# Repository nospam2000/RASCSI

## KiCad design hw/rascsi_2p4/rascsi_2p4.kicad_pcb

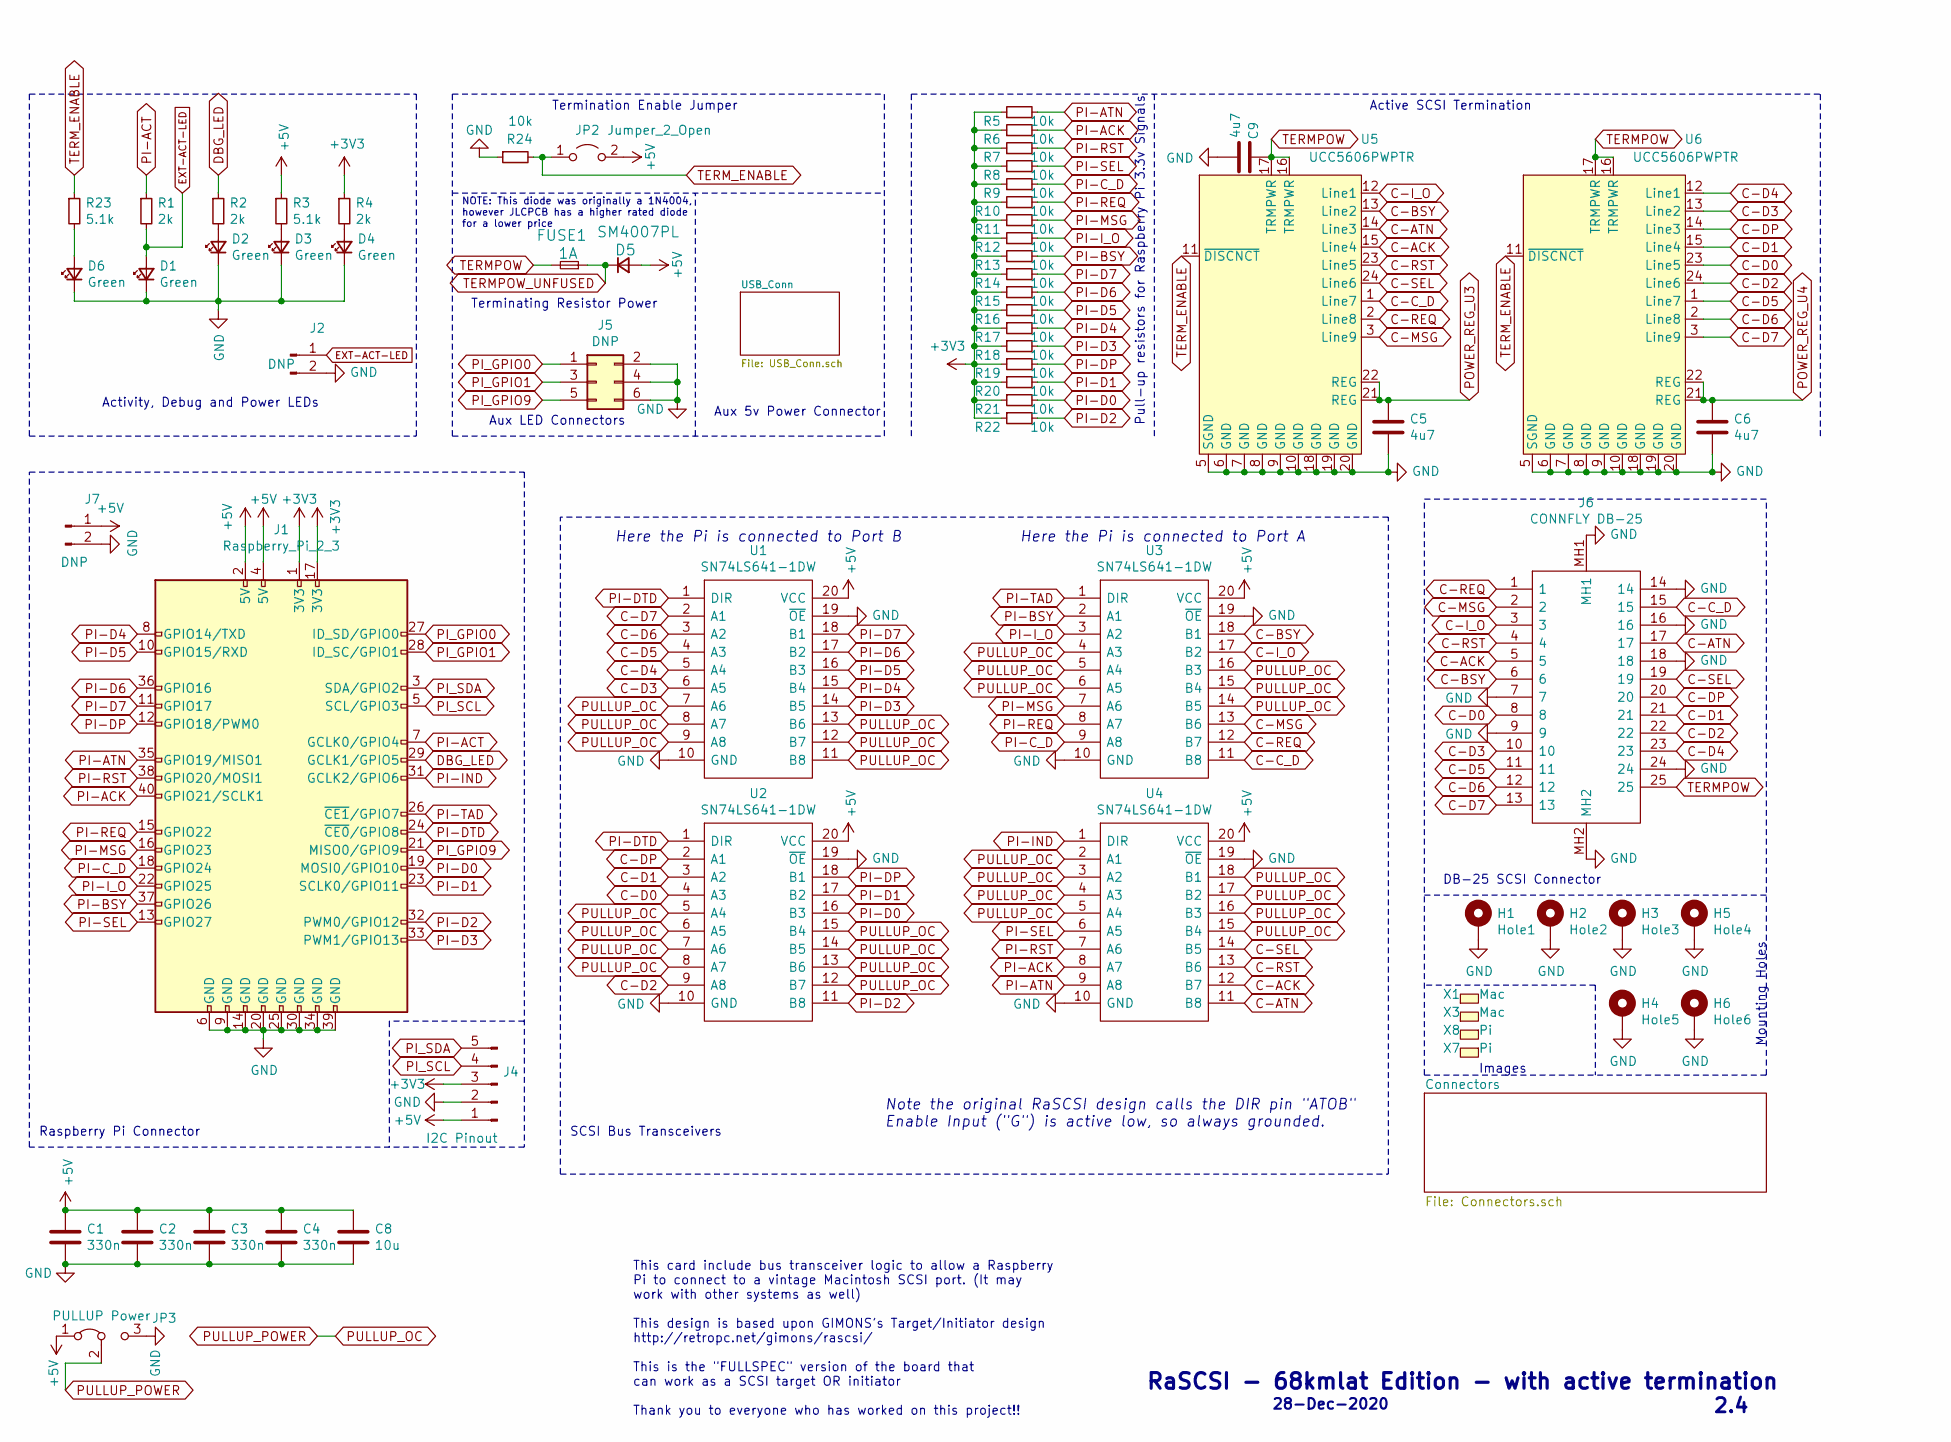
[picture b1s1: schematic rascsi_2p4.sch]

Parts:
C1, C2, C3, C4: 330n; C_0805_2012Metric; Manufacturer_Part_Number 0805B334K500NT; LCSC C1740
C5, C6, C9: 4u7; C_0805_2012Metric; Manufacturer_Part_Number CL21A475KAQNNNE; LCSC C1779
C8: 10u; C_0805_2012Metric; Manufacturer_Part_Number CL21A106KAYNNNE; LCSC C15850
D1, D2, D3, D4, D6: Green; LED_0805_2012Metric; Manufacturer_Part_Number C2297; LCSC C2297
D5: SM4007PL; D_SOD-123F; Manufacturer_Part_Number SM4007PL; LCSC C64898
FUSE1: 1A; Fuse_1206_3216Metric; Manufacturer_Part_Number 12B1100B; LCSC C182974
H1: Hole1; MountingHole_2.7mm_M2.5_Pad_Via; Manufacturer_Part_Number DNP; LCSC DNP
H2: Hole2; MountingHole_2.7mm_M2.5_Pad_Via; Manufacturer_Part_Number DNP; LCSC DNP
H3: Hole3; MountingHole_2.7mm_M2.5_Pad_Via; Manufacturer_Part_Number DNP; LCSC DNP
H4: Hole5; MountingHole_2.7mm_M2.5_Pad_Via; Manufacturer_Part_Number DNP; LCSC DNP
H5: Hole4; MountingHole_2.7mm_M2.5_Pad_Via; Manufacturer_Part_Number DNP; LCSC DNP
H6: Hole6; MountingHole_2.7mm_M2.5_Pad_Via; Manufacturer_Part_Number DNP; LCSC DNP
J1: Raspberry_Pi_2_3; PinSocket_2x20_P2.54mm_Vertical; Manufacturer_Part_Number C50982; LCSC C50982
J2: DNP; PinHeader_1x02_P2.54mm_Horizontal; Manufacturer_Part_Number DNP; LCSC DNP
J4: I2C Pinout; PinSocket_1x05_P2.54mm_Vertical; Manufacturer_Part_Number C50950; LCSC C50950
J5: DNP; PinHeader_2x03_P2.54mm_Vertical; Manufacturer_Part_Number DNP; LCSC DNP
J6: CONNFLY DB-25; L717SDB25PA4CH4F_JLCPCB_hand_mount; Manufacturer_Part_Number DS1037-25FNAKT74-0CC; LCSC C77838
J7: DNP; PinHeader_1x02_P2.54mm_Vertical; Manufacturer_Part_Number DNP; LCSC DNP
JP2: Jumper_2_Open; PinHeader_1x02_P2.54mm_Horizontal
JP3: PULLUP Power; SolderJumper-3_P1.3mm_Bridged12_RoundedPad1.0x1.5mm; Manufacturer_Part_Number DNP; LCSC DNP
R1, R2, R4: 2k; R_0402_1005Metric; Manufacturer_Part_Number 0402WGF2001TCE; LCSC C4109
R3, R23: 5.1k; R_0402_1005Metric; Manufacturer_Part_Number 0402WGF5101TCE; LCSC C25905
R5, R6, R7, R8, R9, R10, R11, R12, R13, R14, R15, R16, R17, R18, R19, R20, R21, R22, R24: 10k; R_0402_1005Metric; Manufacturer_Part_Number 0402WGF1002TCE; LCSC C25744
U1, U2, U3, U4: SN74LS641-1DW; SOIC-20W_7.5x12.8mm_P1.27mm; Mouser Part Number 595-SN74LS641-1DW
U5, U6: UCC5606PWPTR; TSSOP-24_6.1x7.8mm_P0.65mm; LCSC C2649373
X1, X3: Mac; mac_happy_small; Manufacturer_Part_Number N/A; LCSC N/A
X7: Pi; pi_logo; Manufacturer_Part_Number N/A; LCSC N/A
X8: Pi; scsi_logo; Manufacturer_Part_Number N/A; LCSC N/A

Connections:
+3V3: J1.1 (3V3), J1.17 (3V3), J4.3, R4.1, R5.1, R6.1, R7.1, R8.1, R9.1, R10.1, R11.1, R12.1, R13.1, R14.1, R15.1, R16.1, R17.1, R18.1, R19.1, R20.1, R21.1, R22.1
+5V: C1.1, C2.1, C3.1, C4.1, C8.1, D5.2 (A), J1.2 (5V), J1.4 (5V), J4.1, J7.1, JP2.2 (B), JP3.1 (A), R3.1, U1.20 (VCC), U2.20 (VCC), U3.20 (VCC), U4.20 (VCC); also elsewhere on the board
C-ACK: J6.5, U4.12 (B7), U5.15 (Line4); also elsewhere on the board
C-ATN: J6.17, U4.11 (B8), U5.14 (Line3); also elsewhere on the board
C-BSY: J6.6, U3.18 (B1), U5.13 (Line2); also elsewhere on the board
C-C_D: J6.15, U3.11 (B8), U5.1 (Line7); also elsewhere on the board
C-D0: J6.8, U2.4 (A3), U6.23 (Line5); also elsewhere on the board
C-D1: J6.21, U2.3 (A2), U6.15 (Line4); also elsewhere on the board
C-D2: J6.22, U2.9 (A8), U6.24 (Line6); also elsewhere on the board
C-D3: J6.10, U1.6 (A5), U6.13 (Line2); also elsewhere on the board
C-D4: J6.23, U1.5 (A4), U6.12 (Line1); also elsewhere on the board
C-D5: J6.11, U1.4 (A3), U6.1 (Line7); also elsewhere on the board
C-D6: J6.12, U1.3 (A2), U6.2 (Line8); also elsewhere on the board
C-D7: J6.13, U1.2 (A1), U6.3 (Line9); also elsewhere on the board
C-DP: J6.20, U2.2 (A1), U6.14 (Line3); also elsewhere on the board
C-I_O: J6.3, U3.17 (B2), U5.12 (Line1); also elsewhere on the board
C-MSG: J6.2, U3.13 (B6), U5.3 (Line9); also elsewhere on the board
C-REQ: J6.1, U3.12 (B7), U5.2 (Line8); also elsewhere on the board
C-RST: J6.4, U4.13 (B6), U5.23 (Line5); also elsewhere on the board
C-SEL: J6.19, U4.14 (B5), U5.24 (Line6); also elsewhere on the board
DBG_LED: J1.29 (GCLK1/GPIO5), R2.1
EXT-ACT-LED: D1.2 (A), J2.1, R1.2; also elsewhere on the board
GND: C1.2, C2.2, C3.2, C4.2, C5.2, C6.2, C8.2, C9.2, D1.1 (K), D2.1 (K), D3.1 (K), D4.1 (K), D6.1 (K), H1.1, H2.1, H3.1, H4.1, H5.1, H6.1, J1.6 (GND), J1.9 (GND), J1.14 (GND), J1.20 (GND), J1.25 (GND), J1.30 (GND), J1.34 (GND), J1.39 (GND), J2.2, J4.2, J5.2, J5.4, J5.6, J6.7, J6.9, J6.14, J6.16, J6.18, J6.24, J6.MH1, J6.MH2, J7.2, JP3.3 (B), R24.1, U1.10 (GND), U1.19 (~OE), U2.10 (GND), U2.19 (~OE), U3.10 (GND), U3.19 (~OE), U4.10 (GND), U4.19 (~OE), U5.5 (SGND), U5.6 (GND), U5.7 (GND), U5.8 (GND), U5.9 (GND), U5.10 (GND), U5.18 (GND), U5.19 (GND), U5.20 (GND), U6.5 (SGND), U6.6 (GND), U6.7 (GND), U6.8 (GND), U6.9 (GND), U6.10 (GND), U6.18 (GND), U6.19 (GND), U6.20 (GND); also elsewhere on the board
unnamed: D2.2 (A), R2.2
unnamed: D3.2 (A), R3.2
unnamed: D4.2 (A), R4.2
unnamed: D6.2 (A), R23.2
PI-ACK: J1.40 (GPIO21/SCLK1), R6.2, U4.8 (A7)
PI-ACT: J1.7 (GCLK0/GPIO4), R1.1
PI-ATN: J1.35 (GPIO19/MISO1), R5.2, U4.9 (A8)
PI-BSY: J1.37 (GPIO26), R13.2, U3.2 (A1)
PI-C_D: J1.18 (GPIO24), R9.2, U3.9 (A8)
PI-D0: J1.19 (MOSI0/GPIO10), R21.2, U2.16 (B3)
PI-D1: J1.23 (SCLK0/GPIO11), R20.2, U2.17 (B2)
PI-D2: J1.32 (PWM0/GPIO12), R22.2, U2.11 (B8)
PI-D3: J1.33 (PWM1/GPIO13), R18.2, U1.14 (B5)
PI-D4: J1.8 (GPIO14/TXD), R17.2, U1.15 (B4)
PI-D5: J1.10 (GPIO15/RXD), R16.2, U1.16 (B3)
PI-D6: J1.36 (GPIO16), R15.2, U1.17 (B2)
PI-D7: J1.11 (GPIO17), R14.2, U1.18 (B1)
PI-DP: J1.12 (GPIO18/PWM0), R19.2, U2.18 (B1)
PI-DTD: J1.24 (~CE0~/GPIO8), U1.1 (DIR), U2.1 (DIR)
PI-IND: J1.31 (GCLK2/GPIO6), U4.1 (DIR)
PI-I_O: J1.22 (GPIO25), R12.2, U3.3 (A2)
PI-MSG: J1.16 (GPIO23), R11.2, U3.7 (A6)
PI-REQ: J1.15 (GPIO22), R10.2, U3.8 (A7)
PI-RST: J1.38 (GPIO20/MOSI1), R7.2, U4.7 (A6)
PI-SEL: J1.13 (GPIO27), R8.2, U4.6 (A5)
PI-TAD: J1.26 (~CE1~/GPIO7), U3.1 (DIR)
PI_GPIO0: J1.27 (ID_SD/GPIO0), J5.1
PI_GPIO1: J1.28 (ID_SC/GPIO1), J5.3
PI_GPIO9: J1.21 (MISO0/GPIO9), J5.5
PI_SCL: J1.5 (SCL/GPIO3), J4.4
PI_SDA: J1.3 (SDA/GPIO2), J4.5
POWER_REG_U3: C5.1, U5.21 (REG), U5.22 (REG)
POWER_REG_U4: C6.1, U6.21 (REG), U6.22 (REG)
PULLUP_OC: JP3.2 (C), U1.7 (A6), U1.8 (A7), U1.9 (A8), U1.11 (B8), U1.12 (B7), U1.13 (B6), U2.5 (A4), U2.6 (A5), U2.7 (A6), U2.8 (A7), U2.12 (B7), U2.13 (B6), U2.14 (B5), U2.15 (B4), U3.4 (A3), U3.5 (A4), U3.6 (A5), U3.14 (B5), U3.15 (B4), U3.16 (B3), U4.2 (A1), U4.3 (A2), U4.4 (A3), U4.5 (A4), U4.15 (B4), U4.16 (B3), U4.17 (B2), U4.18 (B1)
TERMPOW: C9.1, FUSE1.2, J6.25, U5.16 (TRMPWR), U5.17 (TRMPWR), U6.16 (TRMPWR), U6.17 (TRMPWR); also elsewhere on the board
TERMPOW_UNFUSED: D5.1 (K), FUSE1.1
TERM_ENABLE: JP2.1 (A), R23.1, R24.2, U5.11 (~DISCNCT), U6.11 (~DISCNCT)

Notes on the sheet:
Note the original RaSCSI design calls the DIR pin "ATOB" Enable Input ("G") is active low, so always grounded.
Activity, Debug and Power LEDs
Pull-up resistors for Raspberry Pi 3.3v Signals
Raspberry Pi Connector
Terminating Resistor Power
SCSI Bus Transceivers
DB-25 SCSI Connector
This card include bus transceiver logic to allow a Raspberry Pi to connect to a vintage Macintosh SCSI port. (It may work with other systems as well) This design is based upon GIMONS's Target/Initiator design http://retropc.net/gimons/rascsi/ This is the "FULLSPEC" version of the board that can wor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
Images
Mounting Holes
RaSCSI - 68kmlat Edition - with active termination
2.4
28-Dec-2020
Aux LED Connectors
Aux 5v Power Connector
NOTE: This diode was originally a 1N4004, however JLCPCB has a higher rated diode for a lower price
Active SCSI Termination
Termination Enable Jumper
Here the Pi is connected to Port A
Here the Pi is connected to Port B

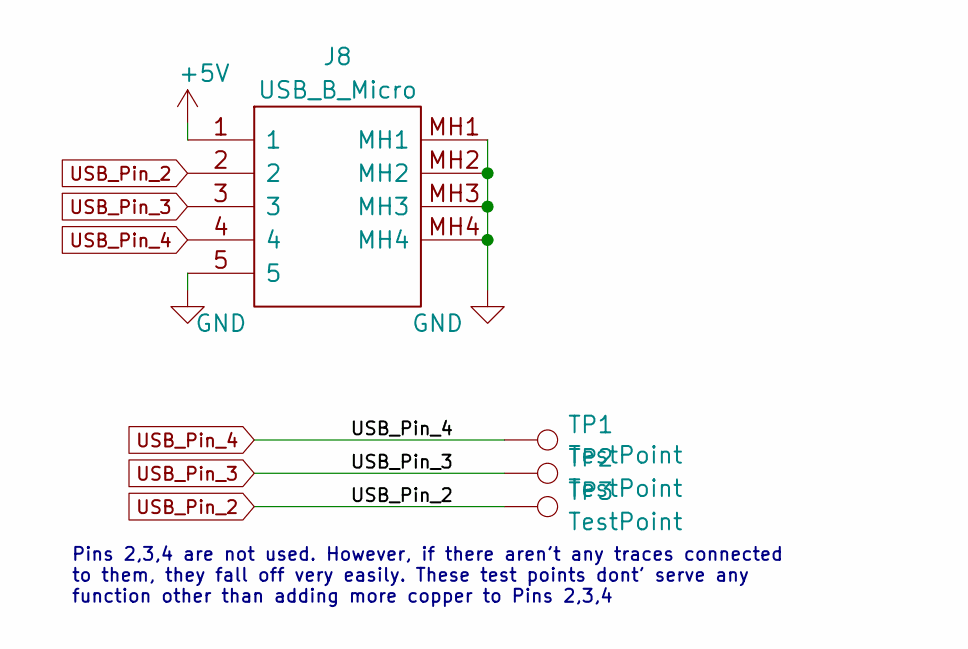
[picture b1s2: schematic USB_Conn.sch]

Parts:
J8: USB_B_Micro; U254051N4BH806_JLCPCB_hand_mount; Manufacturer_Part_Number U254-051N-4BH806; LCSC C319170
TP1, TP2, TP3: TestPoint; TestPoint_Pad_D1.0mm; Manufacturer_Part_Number N/A; LCSC N/A

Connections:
+5V: J8.1; also elsewhere on the board
GND: J8.5, J8.MH1, J8.MH2, J8.MH3, J8.MH4; also elsewhere on the board
USB_Pin_2: J8.2, TP3.1
USB_Pin_3: J8.3, TP2.1
USB_Pin_4: J8.4, TP1.1

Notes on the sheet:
Pins 2,3,4 are not used. However, if there aren't any traces connected to them, they fall off very easily. These test points dont' serve any function other than adding more copper to Pins 2,3,4

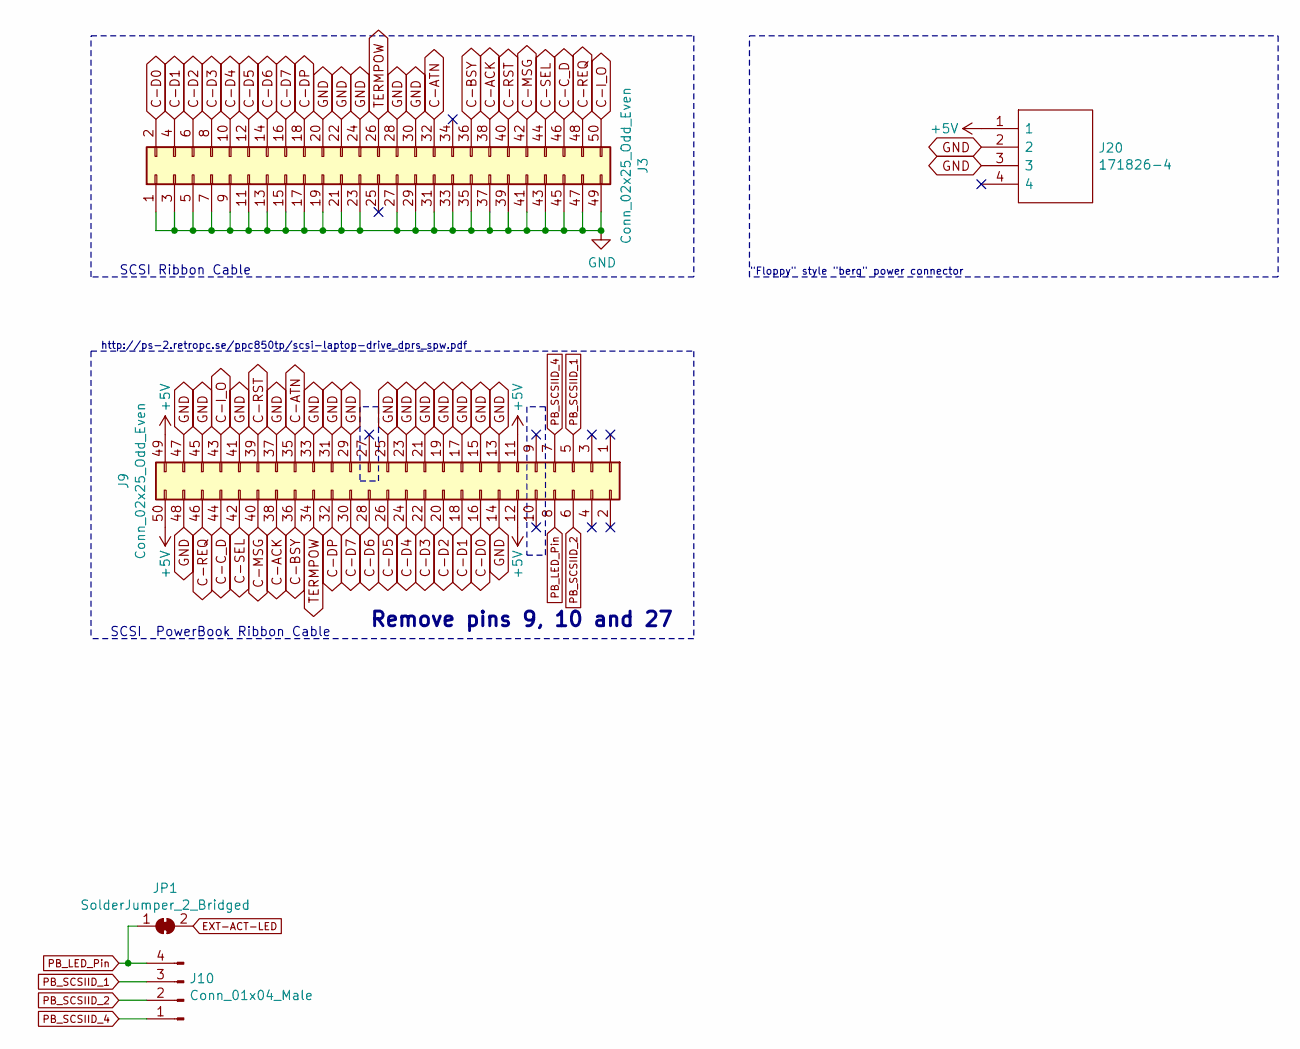
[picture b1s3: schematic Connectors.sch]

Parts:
J3: Conn_02x25_Odd_Even; PinHeader_2x25_P2.54mm_Vertical_JLCPCB_hand_mount; Manufacturer_Part_Number C30006; LCSC C30006
J9: Conn_02x25_Odd_Even; PinHeader_2x25_P2.00mm_Horizontal; Manufacturer_Part_Number C3407; LCSC C3407
J10: Conn_01x04_Male; PinHeader_1x04_P2.00mm_Vertical
J20: 171826-4; SHDRRA4W69P0X250_1X4_1000X1350X670P; Mouser Part Number 571-1718264
JP1: SolderJumper_2_Bridged; SolderJumper-2_P1.3mm_Bridged_Pad1.0x1.5mm

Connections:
+5V: J9.11, J9.12, J9.49, J9.50, J20.1; also elsewhere on the board
C-ACK: J3.38, J9.38; also elsewhere on the board
C-ATN: J3.32, J9.35; also elsewhere on the board
C-BSY: J3.36, J9.36; also elsewhere on the board
C-C_D: J3.46, J9.44; also elsewhere on the board
C-D0: J3.2, J9.16; also elsewhere on the board
C-D1: J3.4, J9.18; also elsewhere on the board
C-D2: J3.6, J9.20; also elsewhere on the board
C-D3: J3.8, J9.22; also elsewhere on the board
C-D4: J3.10, J9.24; also elsewhere on the board
C-D5: J3.12, J9.26; also elsewhere on the board
C-D6: J3.14, J9.28; also elsewhere on the board
C-D7: J3.16, J9.30; also elsewhere on the board
C-DP: J3.18, J9.32; also elsewhere on the board
C-I_O: J3.50, J9.43; also elsewhere on the board
C-MSG: J3.42, J9.40; also elsewhere on the board
C-REQ: J3.48, J9.46; also elsewhere on the board
C-RST: J3.40, J9.39; also elsewhere on the board
C-SEL: J3.44, J9.42; also elsewhere on the board
EXT-ACT-LED: JP1.2 (B); also elsewhere on the board
GND: J3.1, J3.3, J3.5, J3.7, J3.9, J3.11, J3.13, J3.15, J3.17, J3.19, J3.20, J3.21, J3.22, J3.23, J3.24, J3.27, J3.28, J3.29, J3.30, J3.31, J3.33, J3.35, J3.37, J3.39, J3.41, J3.43, J3.45, J3.47, J3.49, J9.13, J9.14, J9.15, J9.17, J9.19, J9.21, J9.23, J9.25, J9.29, J9.31, J9.33, J9.37, J9.41, J9.45, J9.47, J9.48, J20.2, J20.3; also elsewhere on the board
PB_LED_Pin: J9.8, J10.4, JP1.1 (A)
PB_SCSIID_1: J9.5, J10.3
PB_SCSIID_2: J9.6, J10.2
PB_SCSIID_4: J9.7, J10.1
TERMPOW: J3.26, J9.34; also elsewhere on the board

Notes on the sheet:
SCSI Ribbon Cable
SCSI PowerBook Ribbon Cable
http://ps-2.retropc.se/ppc850tp/scsi-laptop-drive_dprs_spw.pdf
Remove pins 9, 10 and 27
"Floppy" style "berg" power connector

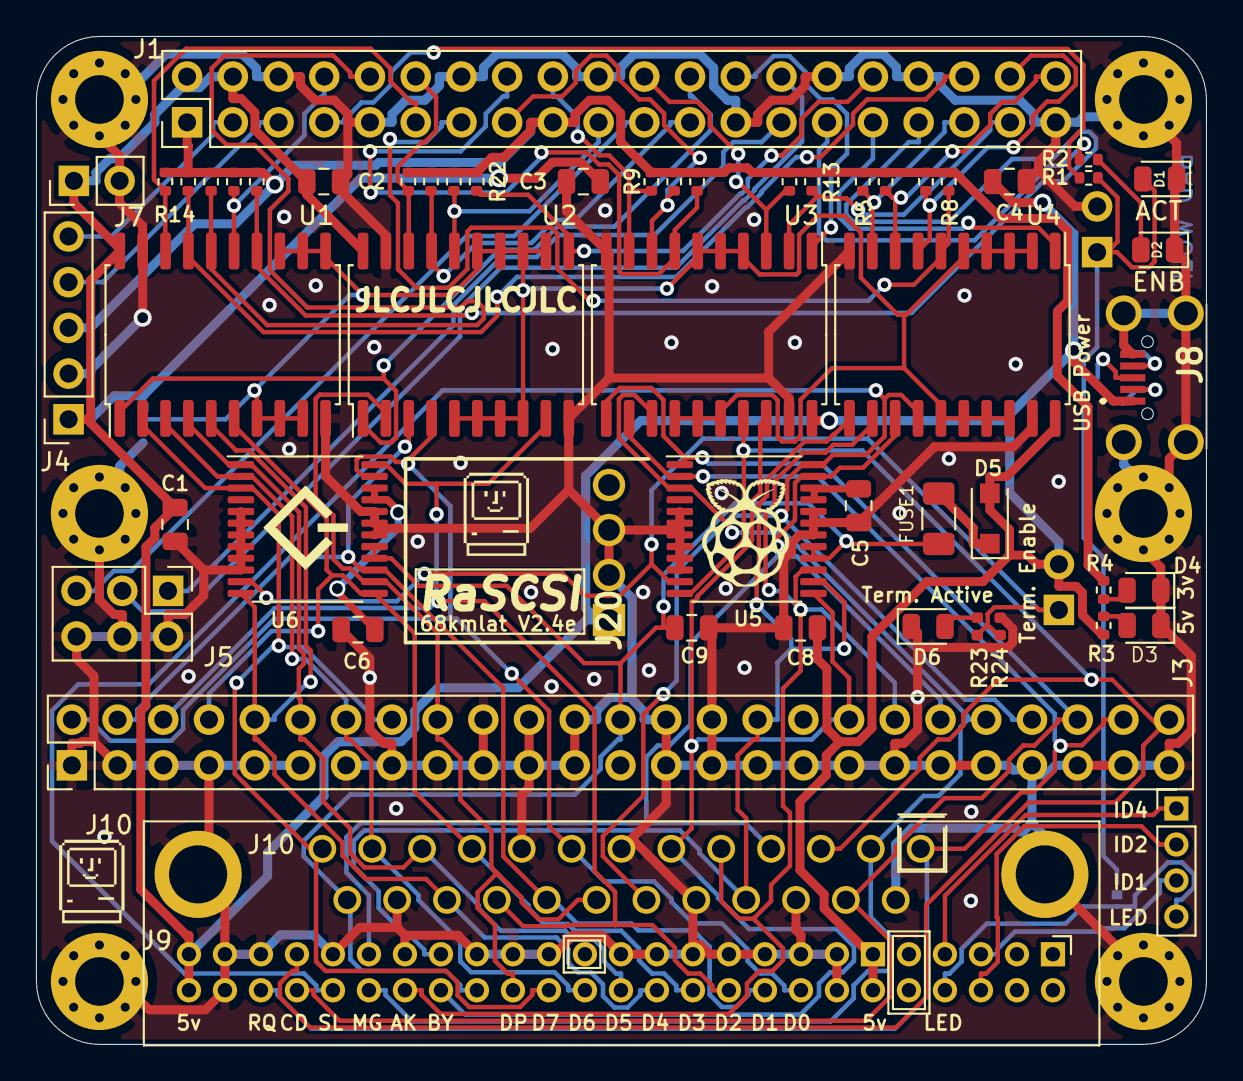
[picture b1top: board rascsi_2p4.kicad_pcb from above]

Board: 2 copper layers, 65.0 x 56.0 mm, 72 parts (0 on the bottom side), 67 nets.

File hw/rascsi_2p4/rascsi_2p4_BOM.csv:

Comment,Designator,Footprint,LCSC
"330n","C1,C2,C3,C4","Capacitor_SMD:C_0805_2012Metric","C1740"
"4u7","C5,C6,C9","Capacitor_SMD:C_0805_2012Metric","C1779"
"10u","C8","Capacitor_SMD:C_0805_2012Metric","C15850"
"Green","D1,D2,D3,D4,D6","LED_SMD:LED_0805_2012Metric","C2297"
"SM4007PL","D5","Diode_SMD:D_SOD-123F","C64898"
"1A","FUSE1","Fuse:Fuse_1206_3216Metric","C182974"
"Hole1","H1","MountingHole:MountingHole_2.7mm_M2.5_Pad_Via","DNP"
"Hole2","H2","MountingHole:MountingHole_2.7mm_M2.5_Pad_Via","DNP"
"Hole3","H3","MountingHole:MountingHole_2.7mm_M2.5_Pad_Via","DNP"
"Hole5","H4","MountingHole:MountingHole_2.7mm_M2.5_Pad_Via","DNP"
"Hole4","H5","MountingHole:MountingHole_2.7mm_M2.5_Pad_Via","DNP"
"Hole6","H6","MountingHole:MountingHole_2.7mm_M2.5_Pad_Via","DNP"
"Raspberry_Pi_2_3","J1","Connector_PinSocket_2.54mm:PinSocket_2x20_P2.54mm_Vertical","C50982"
"Conn_01x04_Male","J10","Connector_PinHeader_2.00mm:PinHeader_1x04_P2.00mm_Vertical",""
"DNP","J2","Connector_PinHeader_2.54mm:PinHeader_1x02_P2.54mm_Horizontal","DNP"
"171826-4","J20","SHDRRA4W69P0X250_1X4_1000X1350X670P",""
"Conn_02x25_Odd_Even","J3","Connector_PinHeader_2.54mm:PinHeader_2x25_P2.54mm_Vertical","C30006"
"I2C Pinout","J4","Connector_PinSocket_2.54mm:PinSocket_1x05_P2.54mm_Vertical","C50950"
"DNP","J5","Connector_PinHeader_2.54mm:PinHeader_2x03_P2.54mm_Vertical","DNP"
"CONNFLY DB-25","J6","SamacSys_Parts:L717SDB25PA4CH4F_JLCPCB_hand_mount","C77838"
"DNP","J7","Connector_PinHeader_2.54mm:PinHeader_1x02_P2.54mm_Vertical","DNP"
"USB_B_Micro","J8","SamacSys_Parts:U254051N4BH806_JLCPCB_hand_mount","C319170"
"Conn_02x25_Odd_Even","J9","Connector_PinHeader_2.00mm:PinHeader_2x25_P2.00mm_Horizontal","C3407"
"SolderJumper_2_Bridged","JP1","Jumper:SolderJumper-2_P1.3mm_Bridged_Pad1.0x1.5mm",""
"Jumper_2_Open","JP2","Connector_PinHeader_2.54mm:PinHeader_1x02_P2.54mm_Horizontal",""
"PULLUP Power","JP3","Jumper:SolderJumper-3_P1.3mm_Bridged12_RoundedPad1.0x1.5mm","DNP"
"2k","R1,R2,R4","Resistor_SMD:R_0402_1005Metric","C4109"
"10k","R5,R6,R7,R8,R9,R10,R11,R12,R13,R14,R15,R16,R17,R18,R19,R20,R21,R22,R24","Resistor_SMD:R_0402_1005Metric","C25744"
"5.1k","R3,R23","Resistor_SMD:R_0402_1005Metric","C25905"
"TestPoint","TP1,TP2,TP3","TestPoint:TestPoint_Pad_D1.0mm","N/A"
"SN74LS641-1DW","U1,U2,U3,U4","Package_SO:SOIC-20W_7.5x12.8mm_P1.27mm","C1548111"
"UCC5606PWPTR","U5,U6","Package_SO:TSSOP-24_6.1x7.8mm_P0.65mm","C2649373"
"Mac","X1,X3","SamacSys_Parts:mac_happy_small","N/A"
"Pi","X7","SamacSys_Parts:pi_logo","N/A"
"Pi","X8","SamacSys_Parts:scsi_logo","N/A"

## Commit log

2021-08-10 Removed obsolete NuvoLink code
2021-08-10 Updated PbDeviceType values
2021-08-10 Added IsScsiDevice, also covering SCRM
2021-08-10 replaced 4x74LS641 by 2x74ALVC164245DGG added pulldowns for floating in/out pins (instead of directly wiring them to ground) setup for autorouting
2021-08-10 added intermediate routing results with 136 vias
2021-08-10 imported routed traces; fixed orientation of U1 and U2
2021-08-10 added U1/U2 caps for 3.3V
2021-08-11 replaced R59-R86 by 100k to reduce power dissipation
2021-08-11 fixed some silkscreen texts removed 2nd JLC... mark fixed overlapping termpower text fixed version on backside
2021-08-11 imported spectra routing data with 111 vias
2021-08-11 fixed rotation of S1
2021-08-11 use active SCSI termination
2021-08-11 moved C7 and fixed some silkscreen text positions
2021-08-11 moved C9 and C8 for successful routing
2021-08-12 added NarrowPowerAdapter to easy routing
2021-08-12 imported routing result with 96 vias
2021-08-12 first routable version
2021-08-13 routed with 99 vias but not imported
2021-08-13 moved components to make space for 50 pin conn
2021-08-14 optimized routing (81 vias)
2021-08-14 added jlcpcb part number of scsi terminator
2021-08-14 changed sild label "Term." by "Termination"
2021-08-14 set BOM fields to DNP
2021-08-14 swapped R18 and R22 slightly moved R14 to R18
2021-08-14 newly routed with 71 vias
2021-08-15 added more GND for cooling term ICs
2021-08-16 made 25pin and USB conn placeable by JLCPCB
2021-12-04 added J3 and J9 to rotation
2021-12-04 fixed logo position changed origin settings and gerber/pos export setting
2021-12-05 fixed part positioning at JLCPCB by removing 2x25 Pin Header from Handmount
2021-12-05 added hand soldering footprint for 2x25 conn to internal lib
2021-12-05 changed /TERM_ENABLE to TERM_ENABLE so that a plugged jumper enables termination
2021-12-05 added solder paste layers
2021-12-05 fixed position of R23 and R24 silk
2021-12-05 increased ground fill
2021-12-07 fixed wiring of U3 and U4 fixed priority of term enable
2021-12-07 imported routing result, added extra GND fill and vias
